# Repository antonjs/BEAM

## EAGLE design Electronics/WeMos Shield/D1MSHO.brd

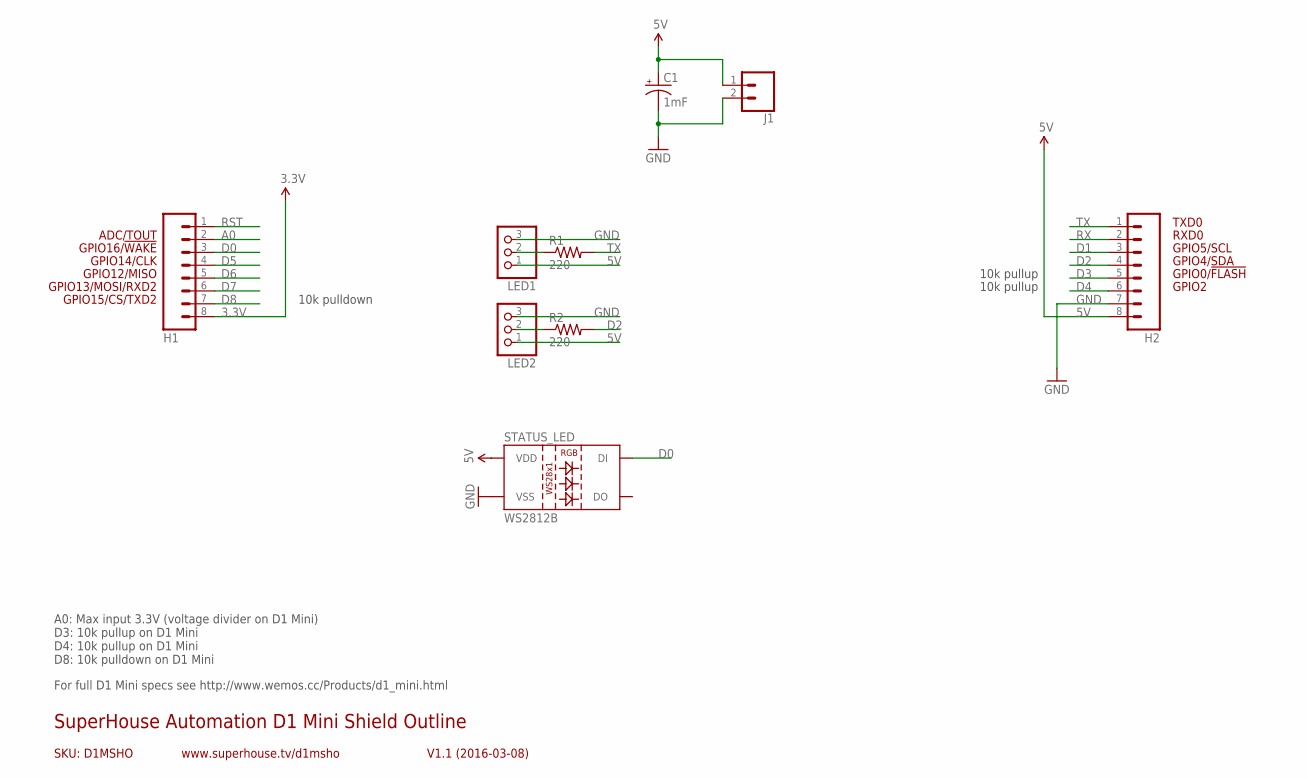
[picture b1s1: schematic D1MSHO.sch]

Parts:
C1: 1mF; CPOL-RADIAL-5MM-10MM
H1, H2: M08; 1X08
J1: CONN_025MM; SCREWTERMINAL-5MM-2
LED1, LED2: PINHD-1X3; 1X03
R1, R2: 220; 0207/10
STATUS_LED: WS2812B

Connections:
3.3V: H1.8
5V: C1.+, H2.8, J1.1, LED1.1, LED2.1, STATUS_LED.1 (VDD)
A0: H1.2
D0: H1.3, STATUS_LED.4 (DI)
D1: H2.3
D2: H2.4, R2.2
D3: H2.5
D4: H2.6
D5: H1.4
D6: H1.5
D7: H1.6
D8: H1.7
GND: C1.-, H2.7, J1.2, LED1.3, LED2.3, STATUS_LED.3 (VSS)
unnamed: LED1.2, R1.1
unnamed: LED2.2, R2.1
RST: H1.1
RX: H2.2
TX: H2.1, R1.2

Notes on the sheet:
GPIO2
GPIO0/!FLASH
GPIO12/MISO
GPIO4/SDA
GPIO5/SCL
RXD0
TXD0
GPIO13/MOSI/RXD2
GPIO14/CLK
GPIO15/CS/TXD2
GPIO16/!WAKE
SKU: D1MSHO
SuperHouse Automation D1 Mini Shield Outline
V1.1 (2016-03-08)
www.superhouse.tv/d1msho
ADC/TOUT
A0: Max input 3.3V (voltage divider on D1 Mini) D3: 10k pullup on D1 Mini D4: 10k pullup on D1 Mini D8: 10k pulldown on D1 Mini
10k pulldown
10k pullup
For full D1 Mini specs see http://www.wemos.cc/Products/d1_mini.html

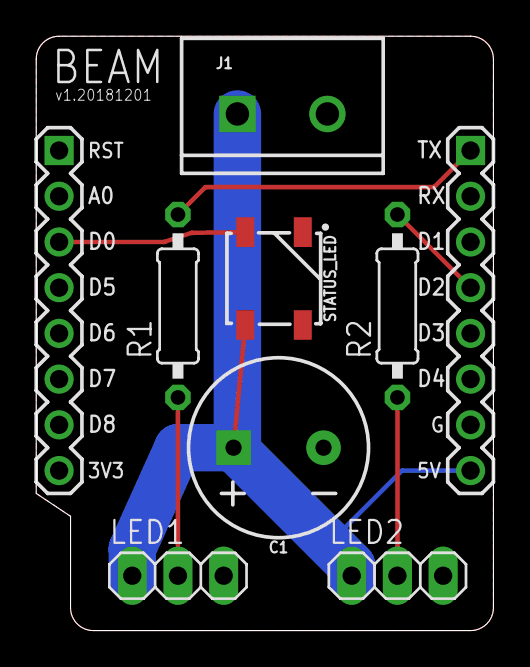
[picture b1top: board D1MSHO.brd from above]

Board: 2 copper layers, 25.4 x 33.0 mm, 9 parts (0 on the bottom side), 7 nets.

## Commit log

2018-08-12 new patterns and updated model
2018-08-12 better sparkles
2018-08-12 Actually commit stuff
2018-09-19 patterns
2018-09-22 Send front and back to seperate universes
2018-09-22 add lxp
2018-12-01 asdf
2018-12-03 add initial pcb design
2018-12-10 bar control
2018-12-10 First pass new firmware
2018-12-10 pcb design
2018-12-12 mirror effect and sin pattern
2018-12-12 OTA update
2018-12-12 Case design
2018-12-15 Gamma output effect
2018-12-15 Case v2
2018-12-15 Untested status led drive code
2018-12-15 Cleanup DS_Store

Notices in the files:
parts and their libraries:
freetronics-original: Licensing: CC v3.0 Share-Alike You are welcome to use this library for commercial purposes.
SparkFun-Connectors: Licensing: Creative Commons ShareAlike 4.0 International - https://creativecommons.org/licenses/by-sa/4.0
